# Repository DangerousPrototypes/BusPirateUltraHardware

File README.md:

# BusPirateUltraHardware
Schematic and PCBs for Bus Pirate Ultra

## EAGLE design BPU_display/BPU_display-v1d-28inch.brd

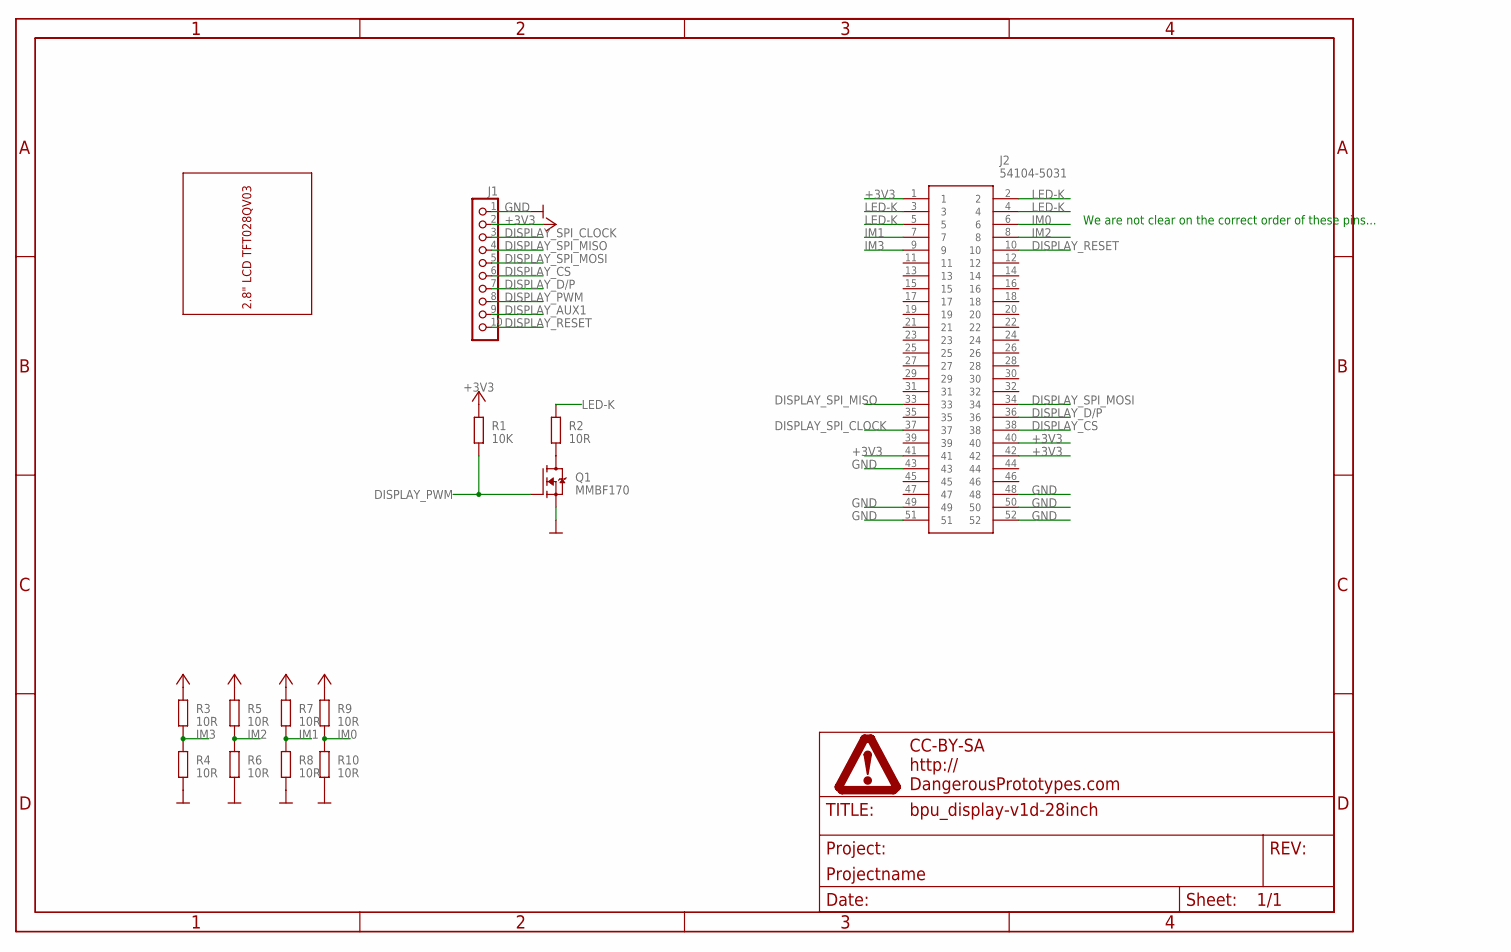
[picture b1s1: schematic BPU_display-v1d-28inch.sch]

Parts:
J1: CON-FPC_X05B20L10T; X05B20L10T
J2: 54104-5031; 541045031
PAGE1: FRAME_DINA4_L; DP_LOGO
Q1: MMBF170; SOT-23
R1: 10K; R0603
R2, R3, R4, R5, R6, R7, R8, R9, R10: 10R; R0603
U$1: LCDS; 2.8INCHLCD

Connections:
+3V3: J1.2, J2.1, J2.40, J2.41, J2.42, R1.2, R3.2, R5.2, R7.2, R9.2
DISPLAY_AUX1: J1.9
DISPLAY_CS: J1.6, J2.38
DISPLAY_D/P: J1.7, J2.36
DISPLAY_PWM: J1.8, Q1.1 (G), R1.1
DISPLAY_RESET: J1.10, J2.10
DISPLAY_SPI_CLOCK: J1.3, J2.37
DISPLAY_SPI_MISO: J1.4, J2.33
DISPLAY_SPI_MOSI: J1.5, J2.34
GND: J1.1, J2.43, J2.48, J2.49, J2.50, J2.51, J2.52, Q1.2 (S), R4.1, R6.1, R8.1, R10.1
IM0: J2.6, R9.1, R10.2
IM1: J2.7, R7.1, R8.2
IM2: J2.8, R5.1, R6.2
IM3: J2.9, R3.1, R4.2
LED-K: J2.2, J2.3, J2.4, J2.5, R2.2
unnamed: Q1.3 (D), R2.1

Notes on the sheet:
We are not clear on the correct order of these pins...

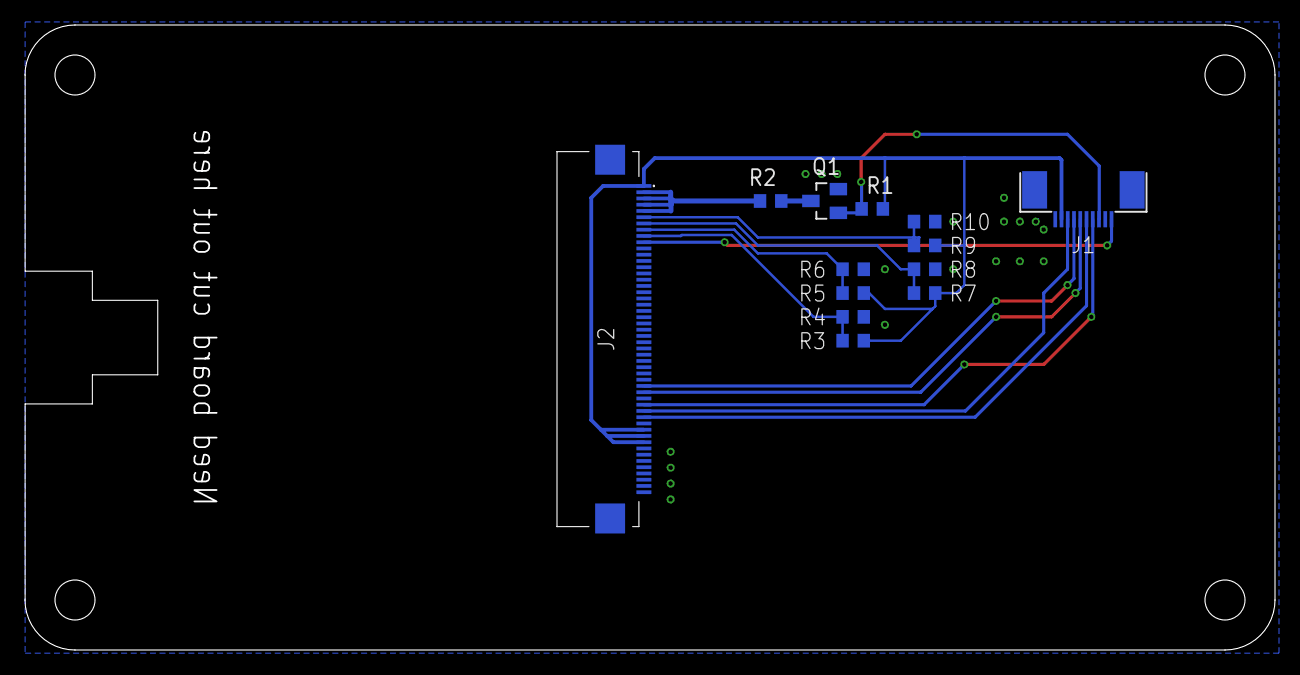
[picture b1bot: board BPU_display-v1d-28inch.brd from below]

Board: 2 copper layers, 100.0 x 50.0 mm, 15 parts (13 on the bottom side), 15 nets.

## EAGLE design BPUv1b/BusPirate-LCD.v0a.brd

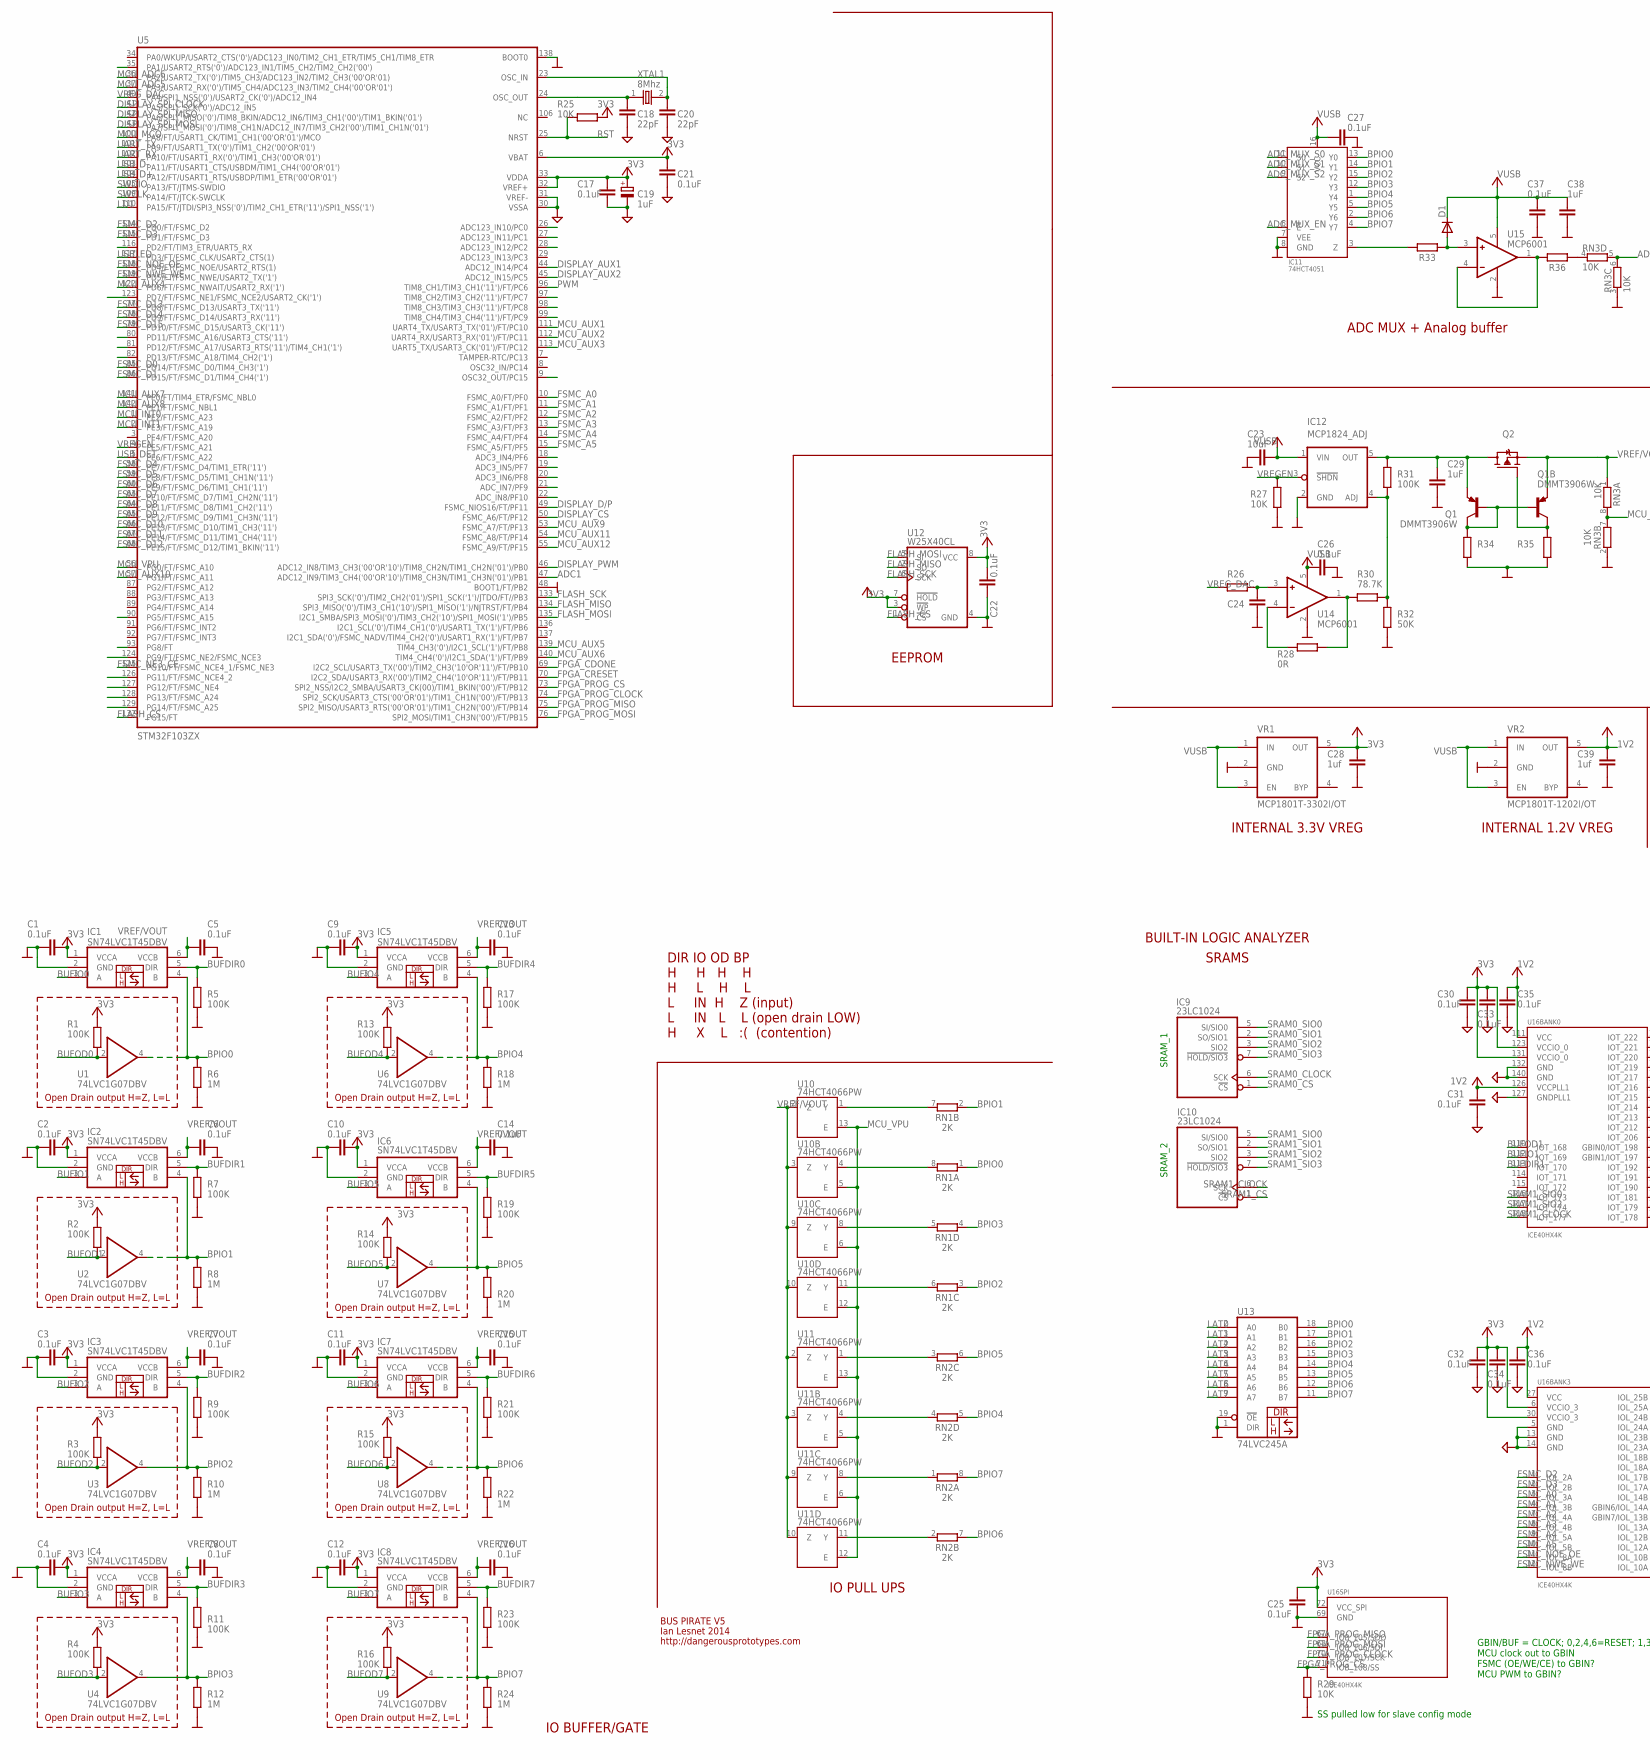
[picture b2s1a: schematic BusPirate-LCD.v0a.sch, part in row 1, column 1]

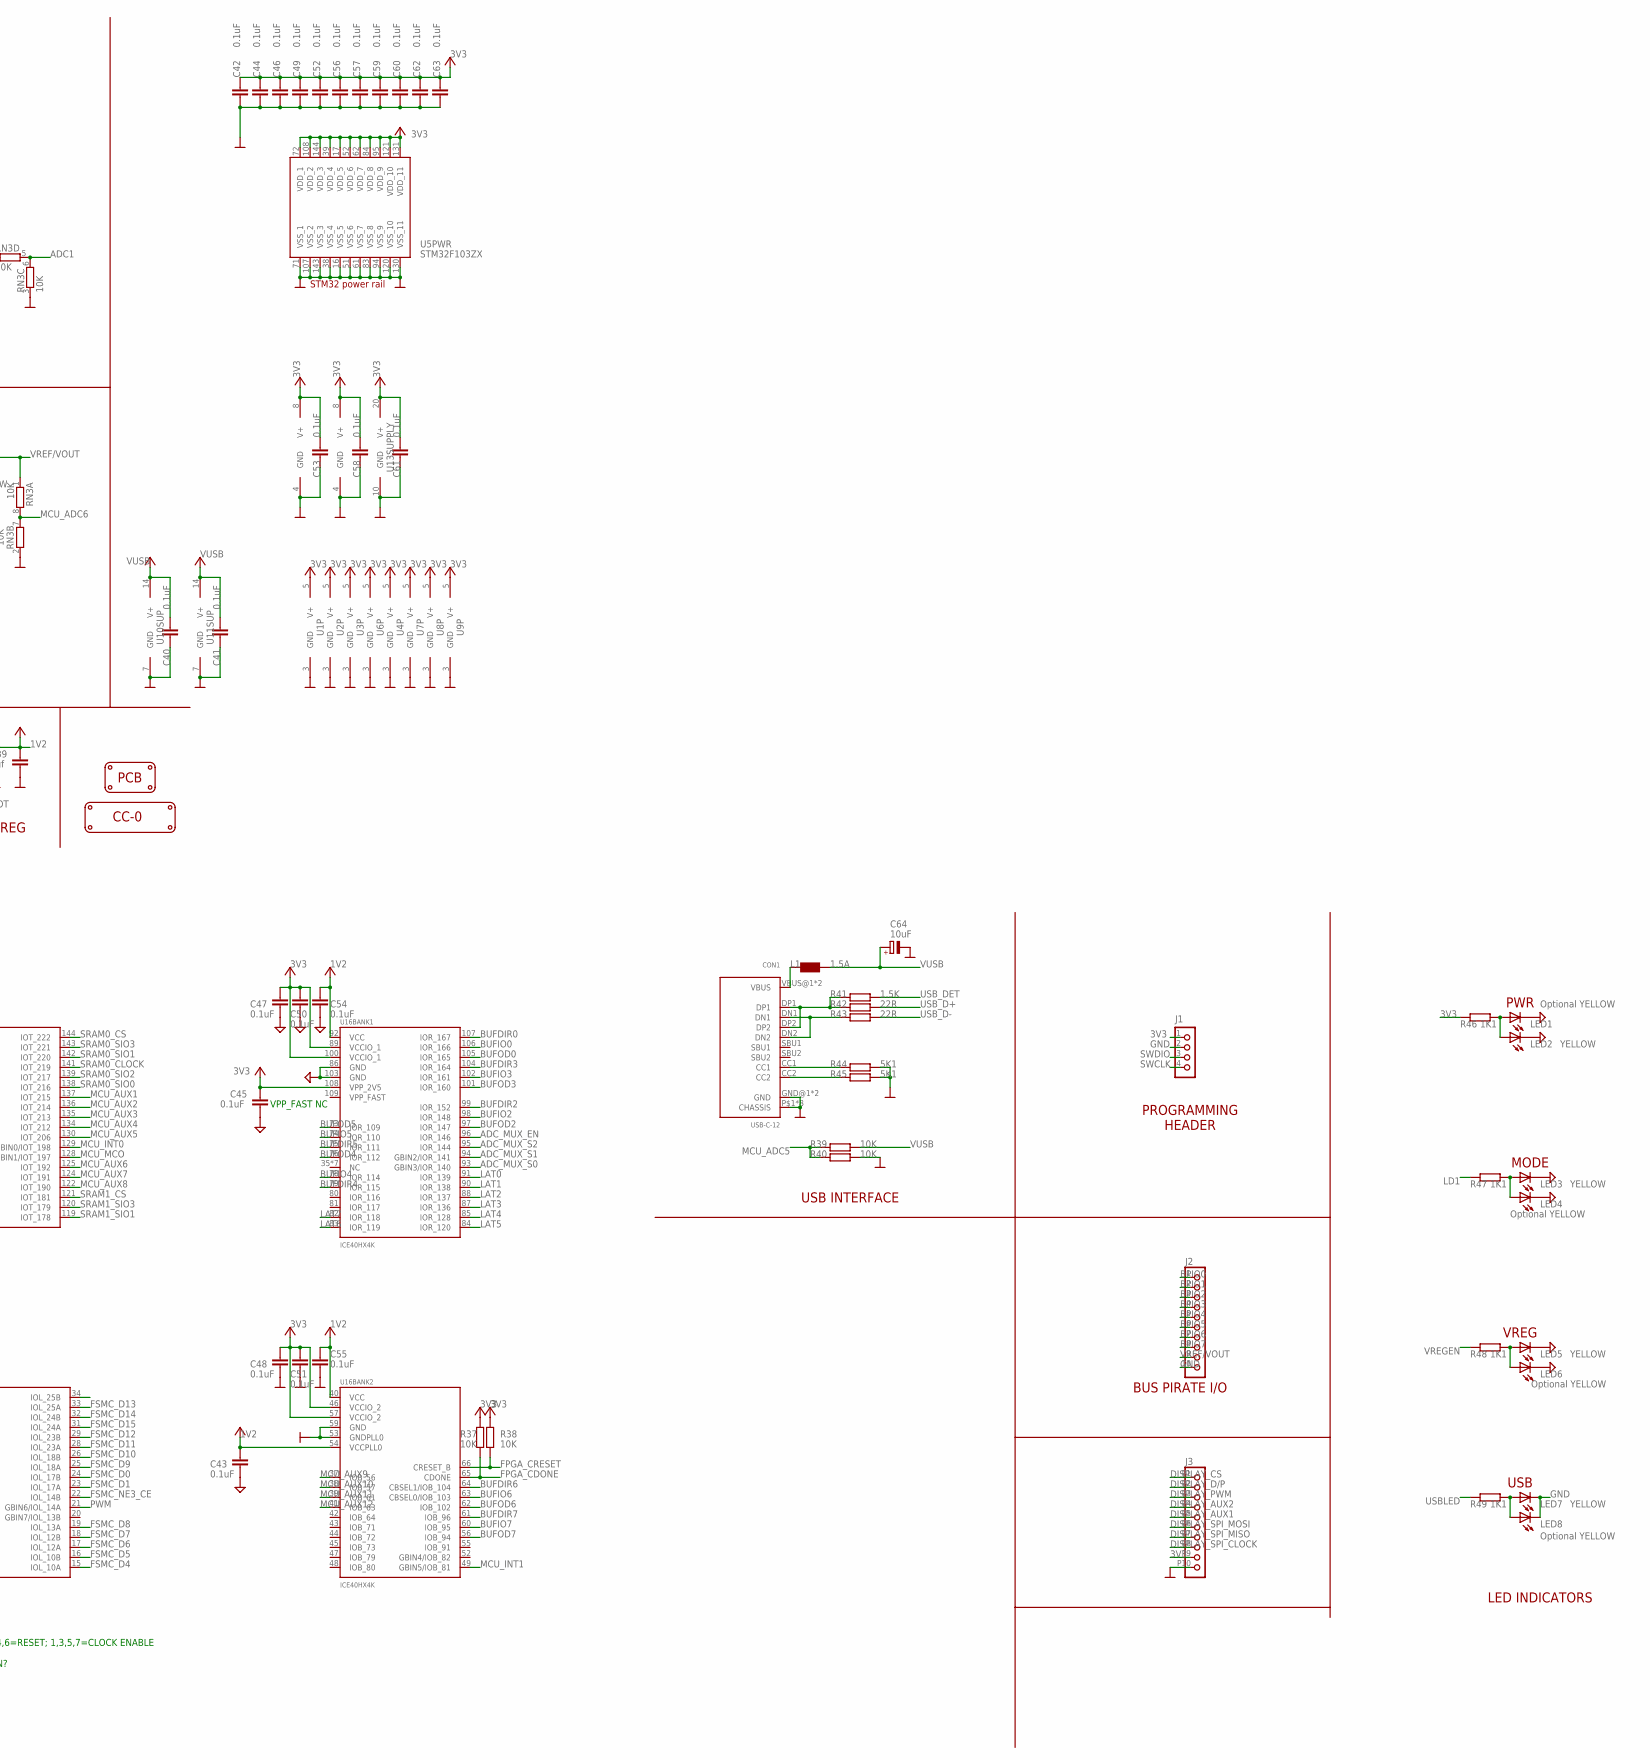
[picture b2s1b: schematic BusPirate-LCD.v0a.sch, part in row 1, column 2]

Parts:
C1, C2, C3, C4, C5, C6, C7, C8, C9, C10, C11, C12, C13, C14, C15, C16: 0.1uF; C0402
C17, C21, C22, C25, C26, C27, C30, C31, C33, C34, C35, C37, C40, C41, C42, C43, C44, C45, C46, C47, C48, C49, C50, C51, C52, C53, C54, C55, C56, C57, C58, C60, C61, C62, C63: 0.1uF; C0603
C18, C20: 22pF; C0603
C19: 1uF; SMC_A
C23: 10uF; C603
C24: C-EUC0603; C0603
C28, C39: 1uf; C0603
C29: 1uF; C603
C32, C36, C59: 0.1uF; C402
C38: 1uF; C0603
C64: 10uF; SMC_A
CON1: USB-C-12; C-31-M-12
D1: DIODE-SOD-123; SOD-123
IC1, IC2, IC3, IC4, IC5, IC6, IC7, IC8: SN74LVC1T45DBV; SC-70-6_EXTENDED_PADS
IC9, IC10: 23LC1024; SOIC-8
IC11: 74HCT4051; TSSOP-16
IC12: MCP1824_ADJ; SOT-23-5
J1: CON_HEADER_1X04; M1X4
J2: CON_HEADER_1X10-RIGHT_ANGLED_PTH_SHROUDED; M1X10_MALE_RIGHT_ANGLES_PTH_SHROUDED
J3: CON_MOLEX_MALE_SMT_SH_1.25; MOLEX_533980771
L1: 1.5A; WE-KI_0805_B
LED1, LED4, LED6, LED8: Optional YELLOW; LED-805
LED2, LED3, LED5, LED7: YELLOW; LED-805
LOGO1: LOGO_CC-0
PCB1: PCB_DP_RECTANGLE-50X100; DP10050_V1
Q1: DMMT3906W; SOT-363
Q2: TRANSISTOR_FET_TSM2301CX; SOT-23
R1, R2, R3, R4, R5, R7, R9, R11, R13, R14, R15, R16, R17, R19, R21, R23: 100K; R0402
R6, R8, R10, R12, R18, R20, R22, R24: 1M; R0402
R25, R27: 10K; R603
R26, R33, R36: R-EU_R0603; R0603
R28: 0R; R603
R29, R37, R38, R39, R40: 10K; R0603
R30: 78.7K; R603
R31: 100K; R603
R32: 50K; R603
R34, R35: RESISTOR-0603; R603
R41: 1.5K; R0603
R42, R43: 22R; R0603
R44, R45: 5K1; R0603
R46, R47, R48, R49: 1K1; R603
RN1, RN2: 2K; RN8P-4R-CRA06S
RN3: 10K; RN8P-4R-CRA06S
U1, U2, U3, U4, U6, U7, U8, U9: 74LVC1G07DBV; SC-70-5_EXTENDED_PADS
U5: STM32F103ZX; TQFP-144
U10, U11: 74HCT4066PW; TSSOP-14
U12: W25X40CL; SOIC-8
U13: 74LVC245A; TSSOP-20
U14, U15: MCP6001; SOT-23-5
U16: ICE40HX4K; TQFP-144
VR1: MCP1801T-3302I/OT; SOT-23-5@1
VR2: MCP1801T-1202I/OT; SOT-23-5@1
XTAL1: 8Mhz; XTAL_4X6

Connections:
1V2: C31.2, C35.2, C36.1, C39.1, C43.2, C54.2, C55.2, U16.27 (VCC), U16.40 (VCC), U16.54 (VCCPLL0), U16.92 (VCC), U16.111 (VCC), U16.126 (VCCPLL1), VR2.5 (OUT)
3V3: C1.1, C2.1, C3.1, C4.1, C9.1, C10.1, C11.1, C12.1, C17.2, C19.+, C21.2, C22.2, C25.2, C28.1, C30.2, C32.1, C33.2, C34.2, C42.2, C44.2, C45.2, C46.2, C47.2, C48.2, C49.2, C50.2, C51.2, C52.2, C53.1, C56.2, C57.2, C58.1, C59.1, C60.2, C61.1, C62.2, C63.2, IC1.1 (VCCA), IC2.1 (VCCA), IC3.1 (VCCA), IC4.1 (VCCA), IC5.1 (VCCA), IC6.1 (VCCA), IC7.1 (VCCA), IC8.1 (VCCA), IC9.8 (V+), IC10.8 (V+), J1.1, J3.P9 (9), R1.2, R2.2, R3.2, R4.2, R13.2, R14.2, R15.2, R16.2, R25.2, R37.2, R38.2, R46.2, U1.5 (V+), U2.5 (V+), U3.5 (V+), U4.5 (V+), U5.6 (VBAT), U5.17 (VDD_5), U5.32 (VREF+), U5.33 (VDDA), U5.39 (VDD_4), U5.52 (VDD_6), U5.62 (VDD_7), U5.72 (VDD_1), U5.84 (VDD_8), U5.95 (VDD_9), U5.108 (VDD_2), U5.121 (VDD_10), U5.131 (VDD_11), U5.144 (VDD_3), U6.5 (V+), U7.5 (V+), U8.5 (V+), U9.5 (V+), U12.3 (!WP), U12.7 (!HOLD), U12.8 (VCC), U13.20 (V+), U16.6 (VCCIO_3), U16.30 (VCCIO_3), U16.46 (VCCIO_2), U16.57 (VCCIO_2), U16.72 (VCC_SPI), U16.89 (VCCIO_1), U16.100 (VCCIO_1), U16.108 (VPP_2V5), U16.123 (VCCIO_0), U16.131 (VCCIO_0), VR1.5 (OUT)
ADC1: RN3.5 (2), RN3.6 (2), U5.47 (ADC12_IN9/TIM3_CH4('00'OR'10')/TIM8_CH3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)
ADC_MUX_EN: IC11.6 (!E), U16.96 (IOR_146)
ADC_MUX_S0: IC11.11 (S0), U16.93 (GBIN3/IOR_140)
ADC_MUX_S1: IC11.10 (S1), U16.94 (GBIN2/IOR_141)
ADC_MUX_S2: IC11.9 (S2), U16.95 (IOR_144)
BPIO0: IC1.4 (B), IC11.13 (Y0), J2.1, R6.2, RN1.1, U1.4 (O), U13.18 (B0)
BPIO1: IC2.4 (B), IC11.14 (Y1), J2.2, R8.2, RN1.2 (1), U2.4 (O), U13.17 (B1)
BPIO2: IC3.4 (B), IC11.15 (Y2), J2.3, R10.2, RN1.3 (1), U3.4 (O), U13.16 (B2)
BPIO3: IC4.4 (B), IC11.12 (Y3), J2.4, R12.2, RN1.4 (1), U4.4 (O), U13.15 (B3)
BPIO4: IC5.4 (B), IC11.1 (Y4), J2.5, R18.2, RN2.5 (2), U6.4 (O), U13.14 (B4)
BPIO5: IC6.4 (B), IC11.5 (Y5), J2.6, R20.2, RN2.6 (2), U7.4 (O), U13.13 (B5)
BPIO6: IC7.4 (B), IC11.2 (Y6), J2.7, R22.2, RN2.7 (2), U8.4 (O), U13.12 (B6)
BPIO7: IC8.4 (B), IC11.4 (Y7), J2.8, R24.2, RN2.8 (2), U9.4 (O), U13.11 (B7)
BUFDIR0: IC1.5 (DIR), R5.2, U16.107 (IOR_167)
BUFDIR1: IC2.5 (DIR), R7.2, U16.113 (IOT_170)
BUFDIR2: IC3.5 (DIR), R9.2, U16.99 (IOR_152)
BUFDIR3: IC4.5 (DIR), R11.2, U16.104 (IOR_164)
BUFDIR4: IC5.5 (DIR), R17.2, U16.79 (IOR_115)
BUFDIR5: IC6.5 (DIR), R19.2, U16.75 (IOR_111)
BUFDIR6: IC7.5 (DIR), R21.2, U16.64 (CBSEL1/IOB_104)
BUFDIR7: IC8.5 (DIR), R23.2, U16.61 (IOB_96)
BUFIO0: IC1.3 (A), U16.106 (IOR_166)
BUFIO1: IC2.3 (A), U16.112 (IOT_169)
BUFIO2: IC3.3 (A), U16.98 (IOR_148)
BUFIO3: IC4.3 (A), U16.102 (IOR_161)
BUFIO4: IC5.3 (A), U16.78 (IOR_114)
BUFIO5: IC6.3 (A), U16.74 (IOR_110)
BUFIO6: IC7.3 (A), U16.63 (CBSEL0/IOB_103)
BUFIO7: IC8.3 (A), U16.60 (IOB_95)
BUFOD0: R1.1, U1.2 (I), U16.105 (IOR_165)
BUFOD1: R2.1, U2.2 (I), U16.110 (IOT_168)
BUFOD2: R3.1, U3.2 (I), U16.97 (IOR_147)
BUFOD3: R4.1, U4.2 (I), U16.101 (IOR_160)
BUFOD4: R13.1, U6.2 (I), U16.76 (IOR_112)
BUFOD5: R14.1, U7.2 (I), U16.73 (IOR_109)
BUFOD6: R15.1, U8.2 (I), U16.62 (IOB_102)
BUFOD7: R16.1, U9.2 (I), U16.56 (IOB_94)
D+: CON1.DP1, CON1.DP2, R41.1, R42.2
D-: CON1.DN1, CON1.DN2, R43.2
DISPLAY_AUX1: J3.P5 (5), U5.44 (ADC12_IN14/PC4)
DISPLAY_AUX2: J3.P4 (4), U5.45 (ADC12_IN15/PC5)
DISPLAY_CS: J3.P1 (1), U5.50 (FSMC_A6/FT/PF12)
DISPLAY_D/P: J3.P2 (2), U5.49 (FSMC_NIOS16/FT/PF11)
DISPLAY_PWM: J3.P3 (3), U5.46 (ADC12_IN8/TIM3_CH3('00'OR'10')/TIM8_CH2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)
DISPLAY_SPI_CLOCK: J3.P8 (8), U5.41 (PA5/SPI1_SCK('0')/ADC12_IN5)
DISPLAY_SPI_MISO: J3.P7 (7), U5.42 (PA6/SPI1_MISO('0')/TIM8_BKIN/ADC12_IN6/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)
DISPLAY_SPI_MOSI: J3.P6 (6), U5.43 (PA7/SPI1_MOSI('0')/TIM8_CH1N/ADC12_IN7/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)
FLASH_CS: U5.132 (PG15/FT), U12.1 (!CS)
FLASH_MISO: U5.134 (SPI3_MISO('0')/TIM3_CH1('10')/SPI1_MISO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), U12.2 (SO)
FLASH_MOSI: U5.135 (I2C1_SMBA/SPI3_MOSI('0')/TIM3_CH2('10')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), U12.5 (SI)
FLASH_SCK: U5.133 (SPI3_SCK('0')/TIM2_CH2('01')/SPI1_SCK('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), U12.6 (SCK)
FPGA_CDONE: R37.1, U5.69 (I2C2_SCL/USART3_TX('00')/TIM2_CH3('10'O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), U16.65 (CDONE)
FPGA_CRESET: R38.1, U5.70 (I2C2_SDA/USART3_RX('00')/TIM2_CH4('10'O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), U16.66 (CRESET_B)
FPGA_PROG_CLOCK: U5.74 (SPI2_SCK/USART3_CTS('00'OR'01')/TIM1_CH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), U16.70 (IOB_107/SCK)
FPGA_PROG_CS: R29.2, U5.73 (SPI2_NSS/I2C2_SMBA/USART3_CK(00)/TIM1_B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), U16.71 (IOB_108/SS)
FPGA_PROG_MISO: U5.75 (SPI2_MISO/USART3_RTS('00'OR'01')/TIM1_C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), U16.67 (IOB_105/SDO)
FPGA_PROG_MOSI: U5.76 (SPI2_MOSI/TIM1_CH3N('00')/FT/PB15), U16.68 (IOB_106/SDI)
FSMC_A0: U5.10 (FSMC_A0/FT/PF0), U16.3 (IOL_3A)
FSMC_A1: U5.11 (FSMC_A1/FT/PF1), U16.4 (IOL_3B)
FSMC_A2: U5.12 (FSMC_A2/FT/PF2), U16.7 (IOL_4A)
FSMC_A3: U5.13 (FSMC_A3/FT/PF3), U16.8 (IOL_4B)
FSMC_A4: U5.14 (FSMC_A4/FT/PF4), U16.9 (IOL_5A)
FSMC_A5: U5.15 (FSMC_A5/FT/PF5), U16.10 (IOL_5B)
FSMC_D0: U5.85 (PD14/FT/FSMC_D0/TIM4_CH3('1')), U16.24 (IOL_17B)
FSMC_D1: U5.86 (PD15/FT/FSMC_D1/TIM4_CH4('1')), U16.23 (IOL_17A)
FSMC_D2: U5.114 (PD0/FT/FSMC_D2), U16.1 (IOL_2A)
FSMC_D3: U5.115 (PD1/FT/FSMC_D3), U16.2 (IOL_2B)
FSMC_D4: U5.58 (PE7/FT/FSMC_D4/TIM1_ETR('11')), U16.15 (IOL_10A)
FSMC_D5: U5.59 (PE8/FT/FSMC_D5/TIM1_CH1N('11')), U16.16 (IOL_10B)
FSMC_D6: U5.60 (PE9/FT/FSMC_D6/TIM1_CH1('11')), U16.17 (IOL_12A)
FSMC_D7: U5.63 (PE10/FT/FSMC_D7/TIM1_CH2N('11')), U16.18 (IOL_12B)
FSMC_D8: U5.64 (PE11/FT/FSMC_D8/TIM1_CH2('11')), U16.19 (IOL_13A)
FSMC_D9: U5.65 (PE12/FT/FSMC_D9/TIM1_CH3N('11')), U16.25 (IOL_18A)
FSMC_D10: U5.66 (PE13/FT/FSMC_D10/TIM1_CH3('11')), U16.26 (IOL_18B)
FSMC_D11: U5.67 (PE14/FT/FSMC_D11/TIM1_CH4('11')), U16.28 (IOL_23A)
FSMC_D12: U5.68 (PE15/FT/FSMC_D12/TIM1_BKIN('11')), U16.29 (IOL_23B)
FSMC_D13: U5.77 (PD8/FT/FSMC_D13/USART3_TX('11')), U16.33 (IOL_25A)
FSMC_D14: U5.78 (PD9/FT/FSMC_D14/USART3_RX('11')), U16.32 (IOL_24B)
FSMC_D15: U5.79 (PD10/FT/FSMC_D15/USART3_CK('11')), U16.31 (IOL_24A)
FSMC_NE3_CE: U5.125 (PG10/FT/FSMC_NCE4_1/FSMC_NE3), U16.22 (IOL_14B)
FSMC_NOE_OE: U5.118 (PD4/FT/FSMC_NOE/USART2_RTS(1)), U16.11 (IOL_8A)
FSMC_NWE_WE: U5.119 (PD5/FT/FSMC_NWE/USART2_TX('1')), U16.12 (IOL_8B)
GND: C1.2, C2.2, C3.2, C4.2, C5.1, C6.1, C7.1, C8.1, C9.2, C10.2, C11.2, C12.2, C13.1, C14.1, C15.1, C16.1, C17.1, C18.1, C19.-, C20.1, C21.1, C22.1, C23.2, C24.2, C25.1, C26.2, C27.2, C28.2, C29.2, C30.1, C31.1, C32.2, C33.1, C34.1, C35.1, C36.2, C37.2, C38.2, C39.2, C40.2, C41.2, C42.1, C43.1, C44.1, C45.1, C46.1, C47.1, C48.1, C49.1, C50.1, C51.1, C52.1, C53.2, C54.1, C55.1, C56.1, C57.1, C58.2, C59.2, C60.1, C61.2, C62.1, C63.1, C64.-, CON1.GND@1 (GND), CON1.GND@2 (GND), CON1.P$1 (CHASSIS), CON1.P$2 (CHASSIS), CON1.P$3 (CHASSIS), CON1.P$4 (CHASSIS), CON1.P$5 (CHASSIS), CON1.P$6 (CHASSIS), CON1.P$7 (CHASSIS), CON1.P$8 (CHASSIS), IC1.2 (GND), IC2.2 (GND), IC3.2 (GND), IC4.2 (GND), IC5.2 (GND), IC6.2 (GND), IC7.2 (GND), IC8.2 (GND), IC9.4 (GND), IC10.4 (GND), IC11.7 (VEE), IC11.8 (GND), IC12.2 (GND), J1.2, J2.10, J3.P10 (10), LED1.C, LED2.C, LED3.C, LED4.C, LED5.C, LED6.C, LED7.C, LED8.C, R5.1, R6.1, R7.1, R8.1, R9.1, R10.1, R11.1, R12.1, R17.1, R18.1, R19.1, R20.1, R21.1, R22.1, R23.1, R24.1, R27.2, R29.1, R32.2, R34.1, R35.1, R40.1, R44.2, R45.2, RN3.2 (1), RN3.3 (1), U1.3 (GND), U2.3 (GND), U3.3 (GND), U4.3 (GND), U5.16 (VSS_5), U5.30 (VSSA), U5.31 (VREF-), U5.38 (VSS_4), U5.48 (BOOT1/FT/PB2), U5.51 (VSS_6), U5.61 (VSS_7), U5.71 (VSS_1), U5.83 (VSS_8), U5.94 (VSS_9), U5.107 (VSS_2), U5.120 (VSS_10), U5.130 (VSS_11), U5.138 (BOOT0), U5.143 (VSS_3), U6.3 (GND), U7.3 (GND), U8.3 (GND), U9.3 (GND), U10.7 (GND), U11.7 (GND), U12.4 (GND), U13.1 (DIR), U13.10 (GND), U13.19 (!OE), U14.2 (V-), U15.2 (V-), U16.5 (GND), U16.13 (GND), U16.14 (GND), U16.53 (GNDPLL0), U16.59 (GND), U16.69 (GND), U16.86 (GND), U16.103 (GND), U16.127 (GNDPLL1), U16.132 (GND), U16.140 (GND), VR1.2 (GND), VR2.2 (GND)
LAT0: U13.2 (A0), U16.91 (IOR_139)
LAT1: U13.3 (A1), U16.90 (IOR_138)
LAT2: U13.4 (A2), U16.88 (IOR_137)
LAT3: U13.5 (A3), U16.87 (IOR_136)
LAT4: U13.6 (A4), U16.85 (IOR_128)
LAT5: U13.7 (A5), U16.84 (IOR_120)
LAT6: U13.8 (A6), U16.83 (IOR_119)
LAT7: U13.9 (A7), U16.82 (IOR_118)
LD1: R47.2, U5.110 (PA15/FT/JTDI/SPI3_NSS('0')/TIM2_CH1_ETR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)
MCU_ADC5: R39.2, R40.2, U5.37 (PA3/USART2_RX('0')/TIM5_CH4/ADC123_IN3/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)
MCU_ADC6: RN3.7 (2), RN3.8 (2), U5.36 (PA2/USART2_TX('0')/TIM5_CH3/ADC123_IN2/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)
MCU_AUX1: U5.111 (UART4_TX/USART3_TX('01')/FT/PC10), U16.137 (IOT_215)
MCU_AUX2: U5.112 (UART4_RX/USART3_RX('01')/FT/PC11), U16.136 (IOT_214)
MCU_AUX3: U5.113 (UART5_TX/USART3_CK('01')/FT/PC12), U16.135 (IOT_213)
MCU_AUX4: U5.122 (PD6/FT/FSMC_NWAIT/USART2_RX('1')), U16.134 (IOT_212)
MCU_AUX5: U5.139 (TIM4_CH3('0')/I2C1_SCL('1')/FT/PB8), U16.130 (IOT_206)
MCU_AUX6: U5.140 (TIM4_CH4('0')/I2C1_SDA('1')/FT/PB9), U16.125 (IOT_192)
MCU_AUX7: U5.141 (PE0/FT/TIM4_ETR/FSMC_NBL0), U16.124 (IOT_191)
MCU_AUX8: U5.142 (PE1/FT/FSMC_NBL1), U16.122 (IOT_190)
MCU_AUX9: U5.53 (FSMC_A7/FT/PF13), U16.37 (IOB_56)
MCU_AUX10: U5.57 (PG1/FT/FSMC_A11), U16.38 (IOB_57)
MCU_AUX11: U5.54 (FSMC_A8/FT/PF14), U16.39 (IOB_61)
MCU_AUX12: U5.55 (FSMC_A9/FT/PF15), U16.41 (IOB_63)
MCU_INT0: U5.1 (PE2/FT/FSMC_A23), U16.129 (GBIN0/IOT_198)
MCU_INT1: U5.2 (PE3/FT/FSMC_A19), U16.49 (GBIN5/IOB_81)
MCU_MCO: U5.100 (PA8/FT/USART1_CK/TIM1_CH1('00'OR'01')/M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), U16.128 (GBIN1/IOT_197)
MCU_VPU: U5.56 (PG0/FT/FSMC_A10), U10.5 (E), U10.6 (E), U10.12 (E), U10.13 (E), U11.5 (E), U11.6 (E), U11.12 (E), U11.13 (E)
unnamed: CON1.VBUS@1 (VBUS), CON1.VBUS@2 (VBUS), L1.2 (1)
unnamed: RN1.7 (2), U10.1 (Y)
unnamed: RN1.8 (2), U10.4 (Y)
unnamed: RN1.5 (2), U10.8 (Y)
unnamed: RN1.6 (2), U10.11 (Y)
unnamed: LED3.A, LED4.A, R47.1
unnamed: LED1.A, LED2.A, R46.1
unnamed: C20.2, U5.23 (OSC_IN), XTAL1.2
unnamed: C18.2, U5.24 (OSC_OUT), XTAL1.1
unnamed: Q1.6 (C), Q2.1 (G), R35.2
unnamed: IC12.4 (ADJ), R30.2, R31.1, R32.1
unnamed: LED7.A, LED8.A, R49.1
unnamed: CON1.CC1, R44.1
unnamed: R28.1, U14.4 (-)
unnamed: LED5.A, LED6.A, R48.1
unnamed: CON1.CC2, R45.1
unnamed: R36.2, RN3.4 (1)
unnamed: R28.2, R30.1, U14.1 (OUT)
unnamed: C29.1, IC12.5 (OUT), Q1.4 (E), Q2.3 (D), R31.2
unnamed: Q1.1 (B), Q1.2 (B), Q1.3 (C), R34.2
unnamed: C24.1, R26.2, U14.3 (+)
unnamed: D1.A, R33.2, U15.3 (+)
unnamed: RN2.3 (1), U11.1 (Y)
unnamed: RN2.4 (1), U11.4 (Y)
unnamed: RN2.1, U11.8 (Y)
unnamed: RN2.2 (1), U11.11 (Y)
unnamed: IC11.3 (Z), R33.1
unnamed: R36.1, U15.1 (OUT), U15.4 (-)
PWM: U5.96 (TIM8_CH1/TIM3_CH1('11')/FT/PC6), U16.21 (GBIN6/IOL_14A)
RST: R25.1, U5.25 (NRST)
SRAM0_CLOCK: IC9.6 (SCK), U16.141 (IOT_219)
SRAM0_CS: IC9.1 (!CS), U16.144 (IOT_222)
SRAM0_SIO0: IC9.5 (SI/SIO0), U16.138 (IOT_216)
SRAM0_SIO1: IC9.2 (SO/SIO1), U16.142 (IOT_220)
SRAM0_SIO2: IC9.3 (SIO2), U16.139 (IOT_217)
SRAM0_SIO3: IC9.7 (!HOLD/SIO3), U16.143 (IOT_221)
SRAM1_CLOCK: IC10.6 (SCK), U16.118 (IOT_177)
SRAM1_CS: IC10.1 (!CS), U16.121 (IOT_181)
SRAM1_SIO0: IC10.5 (SI/SIO0), U16.116 (IOT_173)
SRAM1_SIO1: IC10.2 (SO/SIO1), U16.119 (IOT_178)
SRAM1_SIO2: IC10.3 (SIO2), U16.117 (IOT_174)
SRAM1_SIO3: IC10.7 (!HOLD/SIO3), U16.120 (IOT_179)
SWCLK: J1.4, U5.109 (PA14/FT/JTCK-SWCLK)
SWDIO: J1.3, U5.105 (PA13/FT/JTMS-SWDIO)
UART_RX: U5.102 (PA10/FT/USART1_RX('0')/TIM1_CH3('00'OR'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)
UART_TX: U5.101 (PA9/FT/USART1_TX('0')/TIM1_CH2('00'OR'0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)
USBLED: R49.2, U5.117 (PD3/FT/FSMC_CLK/USART2_CTS(1))
USB_D+: R42.1, U5.104 (PA12/FT/USART1_RTS/USBDP/TIM1_ETR('00'O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)
USB_D-: R43.1, U5.103 (PA11/FT/USART1_CTS/USBDM/TIM1_CH4('00'O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)
USB_DET: R41.2, U5.5 (PE6/FT/FSMC_A22)
VPP_FAST: U16.109 (VPP_FAST)
VREF/VOUT: C5.2, C6.2, C7.2, C8.2, C13.2, C14.2, C15.2, C16.2, IC1.6 (VCCB), IC2.6 (VCCB), IC3.6 (VCCB), IC4.6 (VCCB), IC5.6 (VCCB), IC6.6 (VCCB), IC7.6 (VCCB), IC8.6 (VCCB), J2.9, Q1.5 (E), Q2.2 (S), RN3.1, U10.2 (Z), U10.3 (Z), U10.9 (Z), U10.10 (Z), U11.2 (Z), U11.3 (Z), U11.9 (Z), U11.10 (Z)
VREGEN: IC12.3 (!SHDN), R27.1, R48.2, U5.4 (PE5/FT/FSMC_A21)
VREG_DAC: R26.1, U5.40 (PA4/SPI1_NSS('0')/USART2_CK('0')/ADC12_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)
VUSB: C23.1, C26.1, C27.1, C37.1, C38.1, C40.1, C41.1, C64.+, D1.C, IC11.16 (VCC), IC12.1 (VIN), L1.1 (2), R39.1, U10.14 (V+), U11.14 (V+), U14.5 (V+), U15.5 (V+), VR1.1 (IN), VR1.3 (EN), VR2.1 (IN), VR2.3 (EN)

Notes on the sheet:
BUS PIRATE V5
Ian Lesnet 2014
http://dangerousprototypes.com
SRAMS
IO BUFFER/GATE
BUS PIRATE I/O
PWR
MODE
VREG
PROGRAMMING HEADER
USB
INTERNAL 3.3V VREG
BUILT-IN LOGIC ANALYZER
ADC MUX + Analog buffer
USB INTERFACE
IO PULL UPS
LED INDICATORS
Open Drain output H=Z, L=L
SS pulled low for slave config mode
VPP_FAST NC
GBIN/BUF = CLOCK; 0,2,4,6=RESET; 1,3,5,7=CLOCK ENABLE MCU clock out to GBIN FSMC (OE/WE/CE) to GBIN? MCU PWM to GBIN?
DIR IO OD BP H H H H H L H L L IN H Z (input) L IN L L (open drain LOW) H X L :( (contention)
STM32 power rail
INTERNAL 1.2V VREG
SRAM_1
SRAM_2
EEPROM

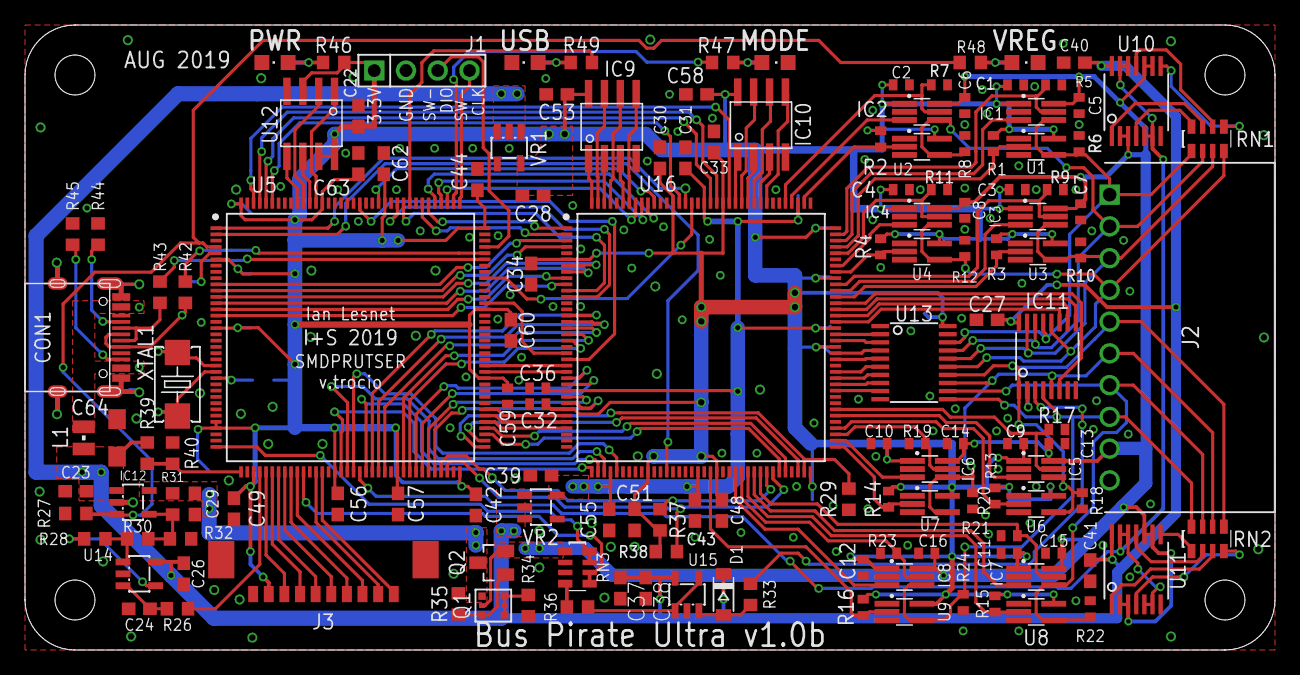
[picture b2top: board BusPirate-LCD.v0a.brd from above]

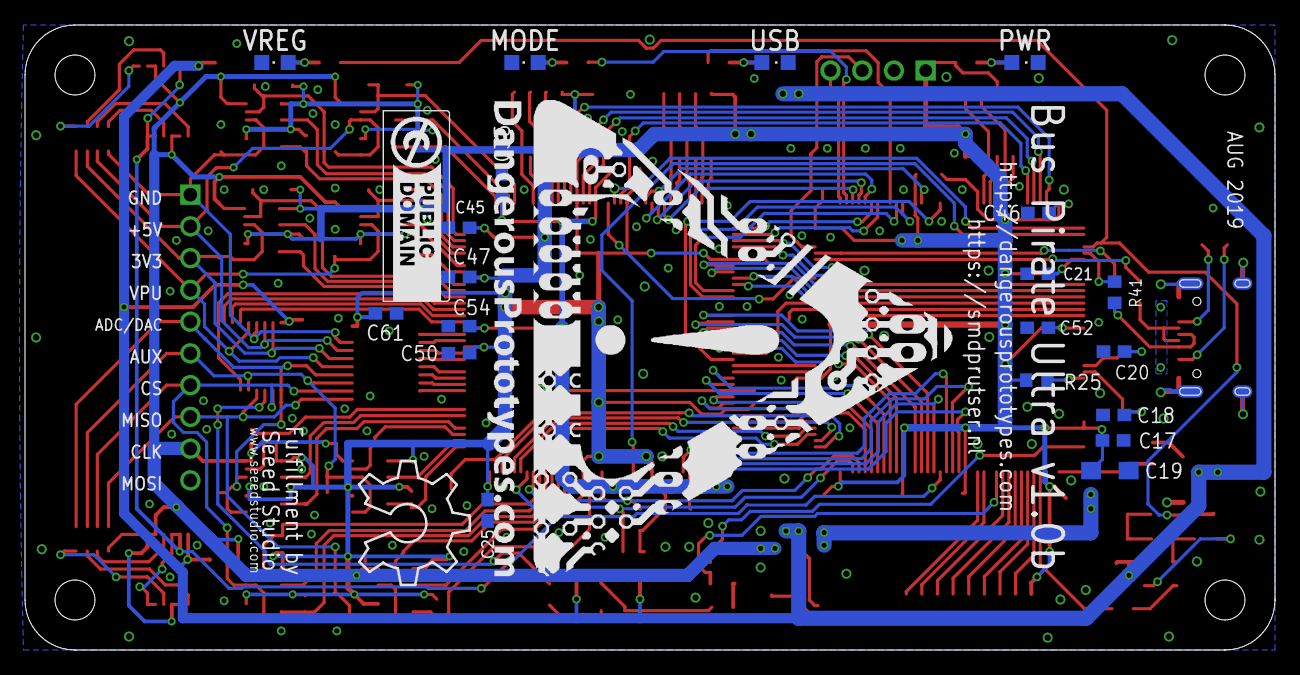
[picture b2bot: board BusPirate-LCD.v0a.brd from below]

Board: 2 copper layers, 100.0 x 50.0 mm, 168 parts (23 on the bottom side), 164 nets.

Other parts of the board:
U$1: DP-LOGO
U$2: OSHW_8X350_NOTEXT
U$4: DP_LOGO_ART_1.5X1.5

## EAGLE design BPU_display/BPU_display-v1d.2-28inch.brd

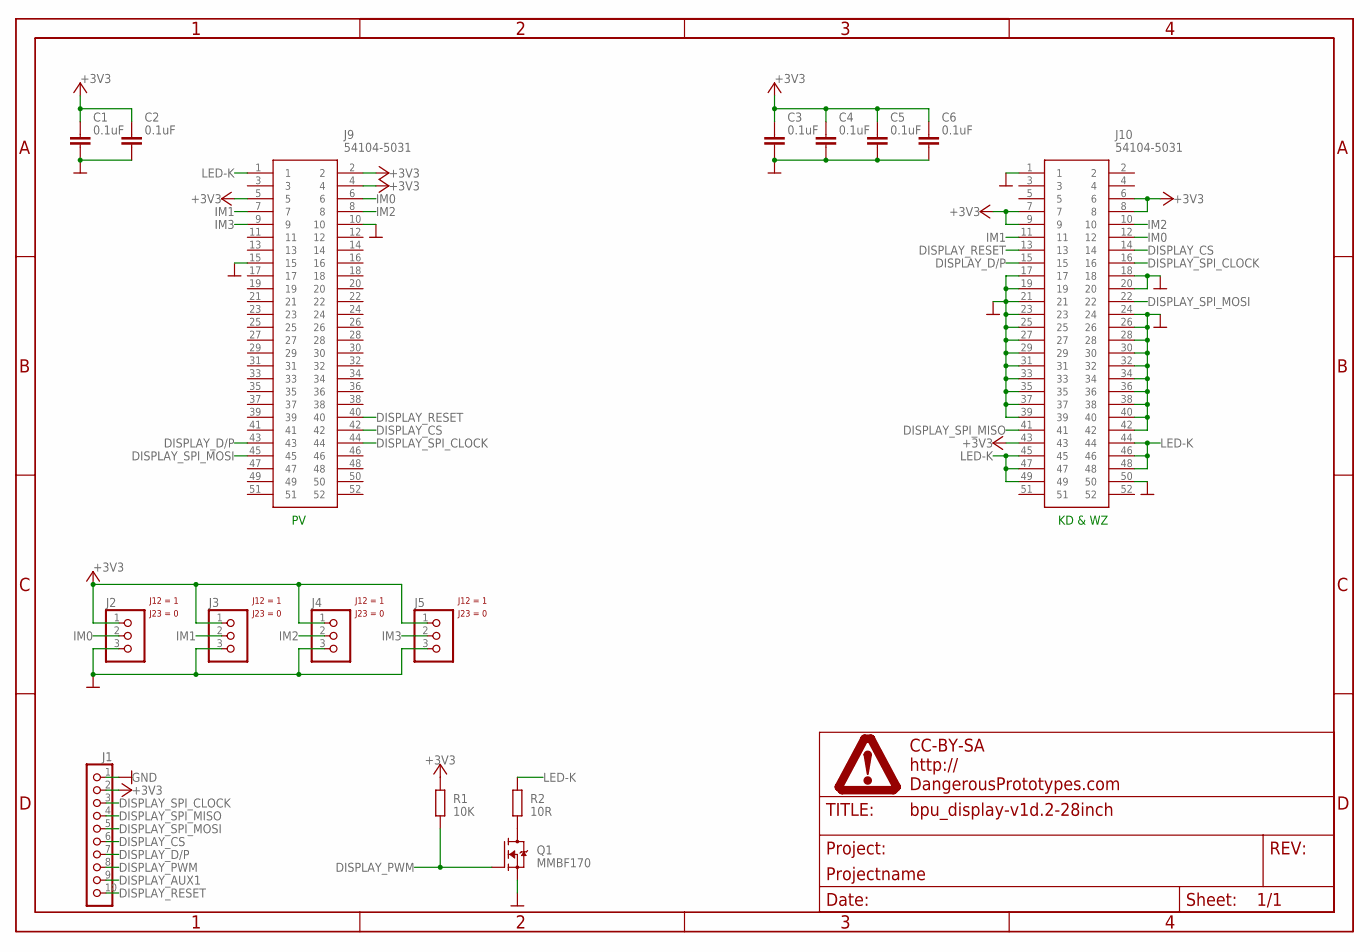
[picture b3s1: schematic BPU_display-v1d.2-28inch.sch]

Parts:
C1, C2, C3, C4, C5, C6: 0.1uF; C603
J1: CON-FPC_X05B20L10T; X05B20L10T
J2, J3, J4, J5: JUMPER_1X30805; JP3_0805
J9, J10: 54104-5031; 541045031
PAGE1: FRAME_DINA4_L; DP_LOGO
Q1: MMBF170; SOT-23
R1: 10K; R0603
R2: 10R; R0603

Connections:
+3V3: C1.1, C2.1, C3.1, C4.1, C5.1, C6.1, J1.2, J2.1, J3.1, J4.1, J5.1, J9.2, J9.4, J9.5, J10.6, J10.7, J10.8, J10.9, J10.43, R1.2
DISPLAY_AUX1: J1.9
DISPLAY_CS: J1.6, J9.42, J10.14
DISPLAY_D/P: J1.7, J9.43, J10.15
DISPLAY_PWM: J1.8, Q1.1 (G), R1.1
DISPLAY_RESET: J1.10, J9.40, J10.13
DISPLAY_SPI_CLOCK: J1.3, J9.44, J10.16
DISPLAY_SPI_MISO: J1.4, J10.41
DISPLAY_SPI_MOSI: J1.5, J9.45, J10.22
GND: C1.2, C2.2, C3.2, C4.2, C5.2, C6.2, J1.1, J2.3, J3.3, J4.3, J5.3, J9.10, J9.15, J10.1, J10.17, J10.18, J10.19, J10.20, J10.21, J10.23, J10.24, J10.25, J10.26, J10.27, J10.28, J10.29, J10.30, J10.31, J10.32, J10.33, J10.34, J10.35, J10.36, J10.37, J10.38, J10.39, J10.40, J10.42, J10.50, Q1.2 (S)
IM0: J2.2, J9.6, J10.12
IM1: J3.2, J9.7, J10.11
IM2: J4.2, J9.8, J10.10
IM3: J5.2, J9.9
LED-K: J9.1, J10.44, J10.45, J10.46, J10.47, J10.48, J10.49, R2.2
unnamed: Q1.3 (D), R2.1

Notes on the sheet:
KD & WZ

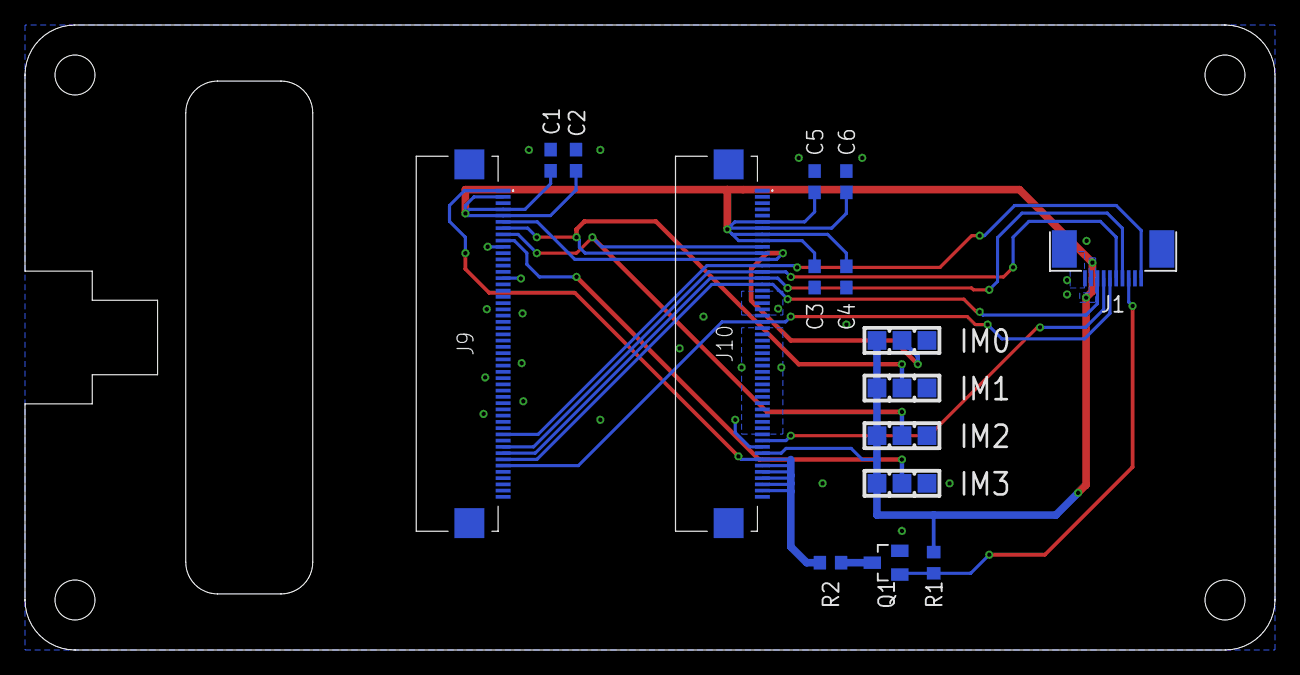
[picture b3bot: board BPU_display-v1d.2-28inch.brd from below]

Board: 2 copper layers, 100.0 x 50.0 mm, 17 parts (16 on the bottom side), 15 nets.

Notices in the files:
BPU_display/BPU_display-v1d-20inch.brd:
LICENSE: CC-BY-SA
